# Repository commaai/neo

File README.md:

neo
=====

<b>NOTE: The NEO is deprecated. Check out the [latest hardware](https://github.com/commaai/hardware).

The neo is an open source robotics research platform. It is powered by a OnePlus 3 smartphone and an [STM32F205](http://www.st.com/en/microcontrollers/stm32f2x5.html?querycriteria=productId=LN1433)-based CAN interface board, in a 3d-printed housing with active cooling.

The neo platform includes [NEOS](https://github.com/commaai/eon-neos), a stripped down Android ROM designed for robustness and to get out of the way of your software. It also provides a modern linux environment for easy development.

Why
------

You cannot get a higher performance embedded processor than what's shipping in modern smartphones. They also come with an impressive array of sensors and radios, and are very low cost.

For some background see the work of [Android Based Robots](http://www.socsci.uci.edu/~jkrichma/ABR/abr_background.html).

Build
------

The neo is designed to be very easy to construct. You need to be able to shop online and use a soldering iron.

There is a **[very detailed guide](https://github.com/commaai/neo/raw/master/guide.pdf)** with instructions on what to order and how to build a neo.

to build a neo, 6 orders must be placed from the following sources:
- digikey
- mcmaster
- shapeways
- oshpark
- amazon
- oneplus

The total cost is about $700.

Directory structure
------

- board -- EagleCAD schematic, board, and library files
- parts -- csv bill of materials
- case -- stl files for 3d printing

Licensing
------

neo research platform is released under the MIT license.

**THIS IS ALPHA QUALITY SOFTWARE FOR RESEARCH PURPOSES ONLY. THIS IS NOT A PRODUCT.
YOU ARE RESPONSIBLE FOR COMPLYING WITH LOCAL LAWS AND REGULATIONS.
NO WARRANTY EXPRESSED OR IMPLIED.**

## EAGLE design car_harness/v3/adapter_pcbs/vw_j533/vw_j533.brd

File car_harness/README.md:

car harness
===

This is the documentation for the 26 pin connector on the car harness.

The car harness currently supports Honda Nidec, Honda Bosch, and Toyota. We would like to support more cars in the future.

Pull requests for additional pin outs are welcome. Please reference the open_pinout.sch.pdf file for adding new cars. This will guarantee the harness will work properly.

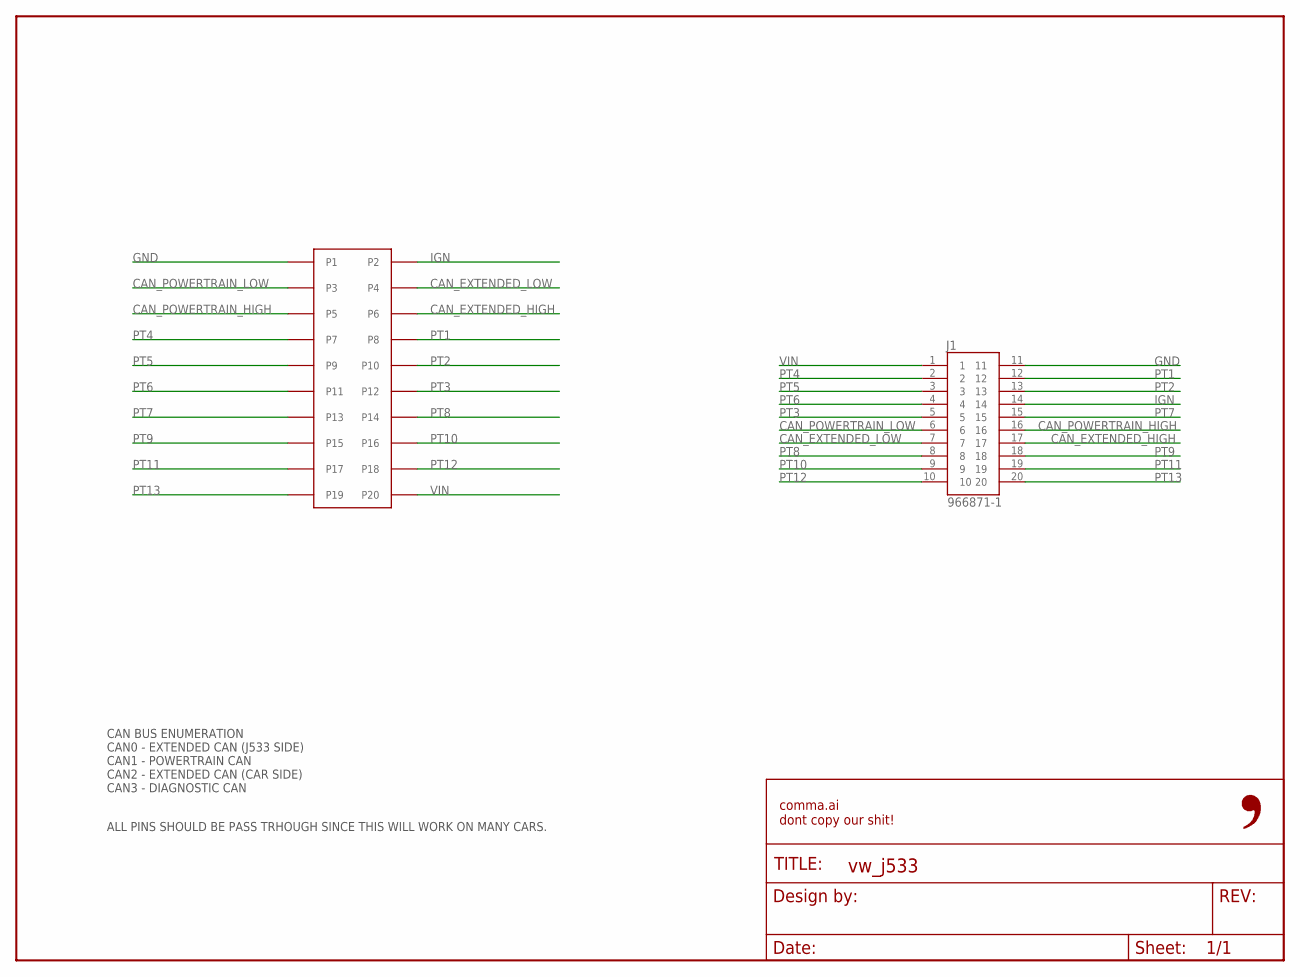
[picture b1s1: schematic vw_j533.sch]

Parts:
FRAME1: FRAME-LETTERNO_PACKAGE; DUMMY
J1: 966871-1; TE_966871-1
J2: 5018762040

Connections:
CAN_EXTENDED_HIGH: J1.17, J2.P6
CAN_EXTENDED_LOW: J1.7, J2.P4
CAN_POWERTRAIN_HIGH: J1.16, J2.P5
CAN_POWERTRAIN_LOW: J1.6, J2.P3
GND: J1.11, J2.P1
IGN: J1.14, J2.P2
PT1: J1.12, J2.P8
PT2: J1.13, J2.P10
PT3: J1.5, J2.P12
PT4: J1.2, J2.P7
PT5: J1.3, J2.P9
PT6: J1.4, J2.P11
PT7: J1.15, J2.P13
PT8: J1.8, J2.P14
PT9: J1.18, J2.P15
PT10: J1.9, J2.P16
PT11: J1.19, J2.P17
PT12: J1.10, J2.P18
PT13: J1.20, J2.P19
VIN: J1.1, J2.P20

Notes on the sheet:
CAN BUS ENUMERATION CAN0 - EXTENDED CAN (J533 SIDE) CAN1 - POWERTRAIN CAN CAN2 - EXTENDED CAN (CAR SIDE) CAN3 - DIAGNOSTIC CAN
ALL PINS SHOULD BE PASS TRHOUGH SINCE THIS WILL WORK ON MANY CARS.

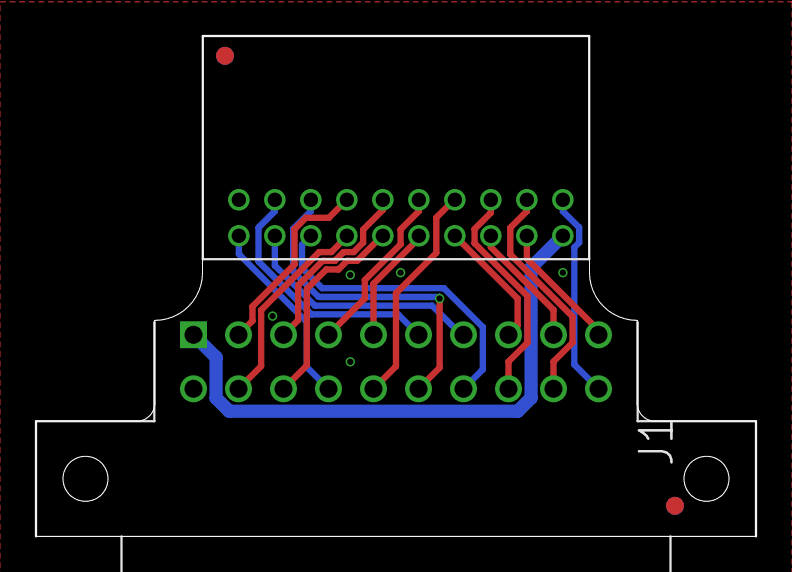
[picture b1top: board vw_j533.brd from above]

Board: 2 copper layers, 40.0 x 27.8 mm, 6 parts (1 on the bottom side), 20 nets.

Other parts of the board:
U$1: LOGO
U$2, U$3: FIDUCIAL

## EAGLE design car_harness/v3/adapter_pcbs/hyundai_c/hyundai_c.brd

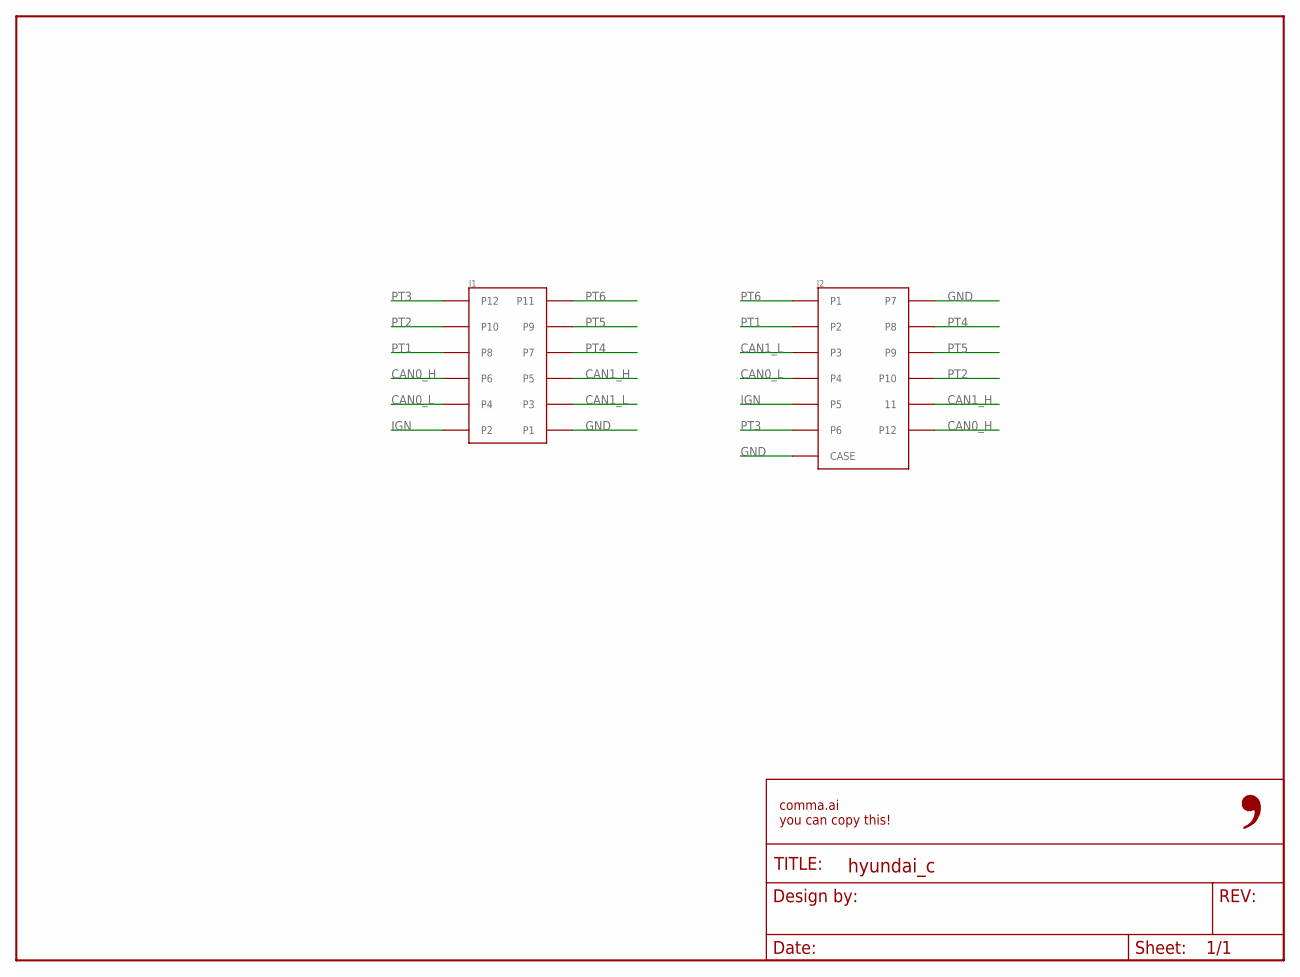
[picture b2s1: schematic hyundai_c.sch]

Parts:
FRAME1: FRAME-LETTER-OPENNO_PACKAGE; DUMMY
J1: 5018761240
J2: MG645845

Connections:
CAN0_H: J1.P6, J2.P12
CAN0_L: J1.P4, J2.P4
CAN1_H: J1.P5, J2.P11 (11)
CAN1_L: J1.P3, J2.P3
GND: J1.P1, J2.P7, J2.P$1 (CASE), J2.P$2 (CASE)
IGN: J1.P2, J2.P5
PT1: J1.P8, J2.P2
PT2: J1.P10, J2.P10
PT3: J1.P12, J2.P6
PT4: J1.P7, J2.P8
PT5: J1.P9, J2.P9
PT6: J1.P11, J2.P1

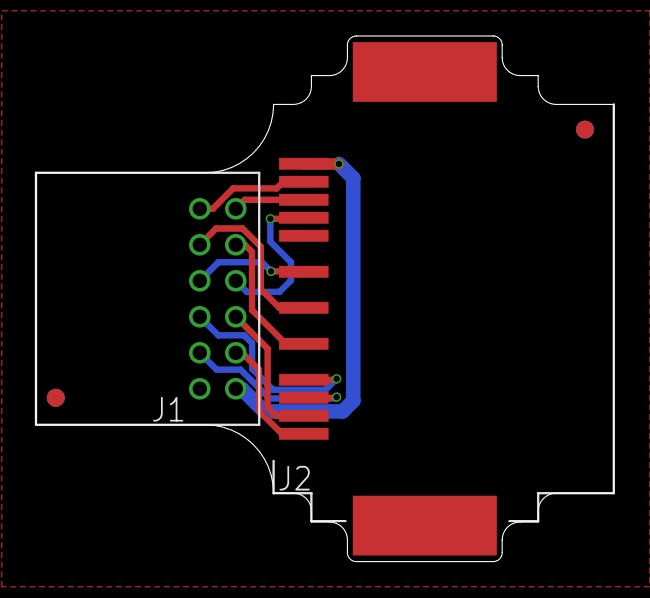
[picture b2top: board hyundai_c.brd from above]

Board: 2 copper layers, 32.1 x 29.2 mm, 6 parts (1 on the bottom side), 12 nets.

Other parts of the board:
U$1: LOGO
U$2, U$3: FIDUCIAL

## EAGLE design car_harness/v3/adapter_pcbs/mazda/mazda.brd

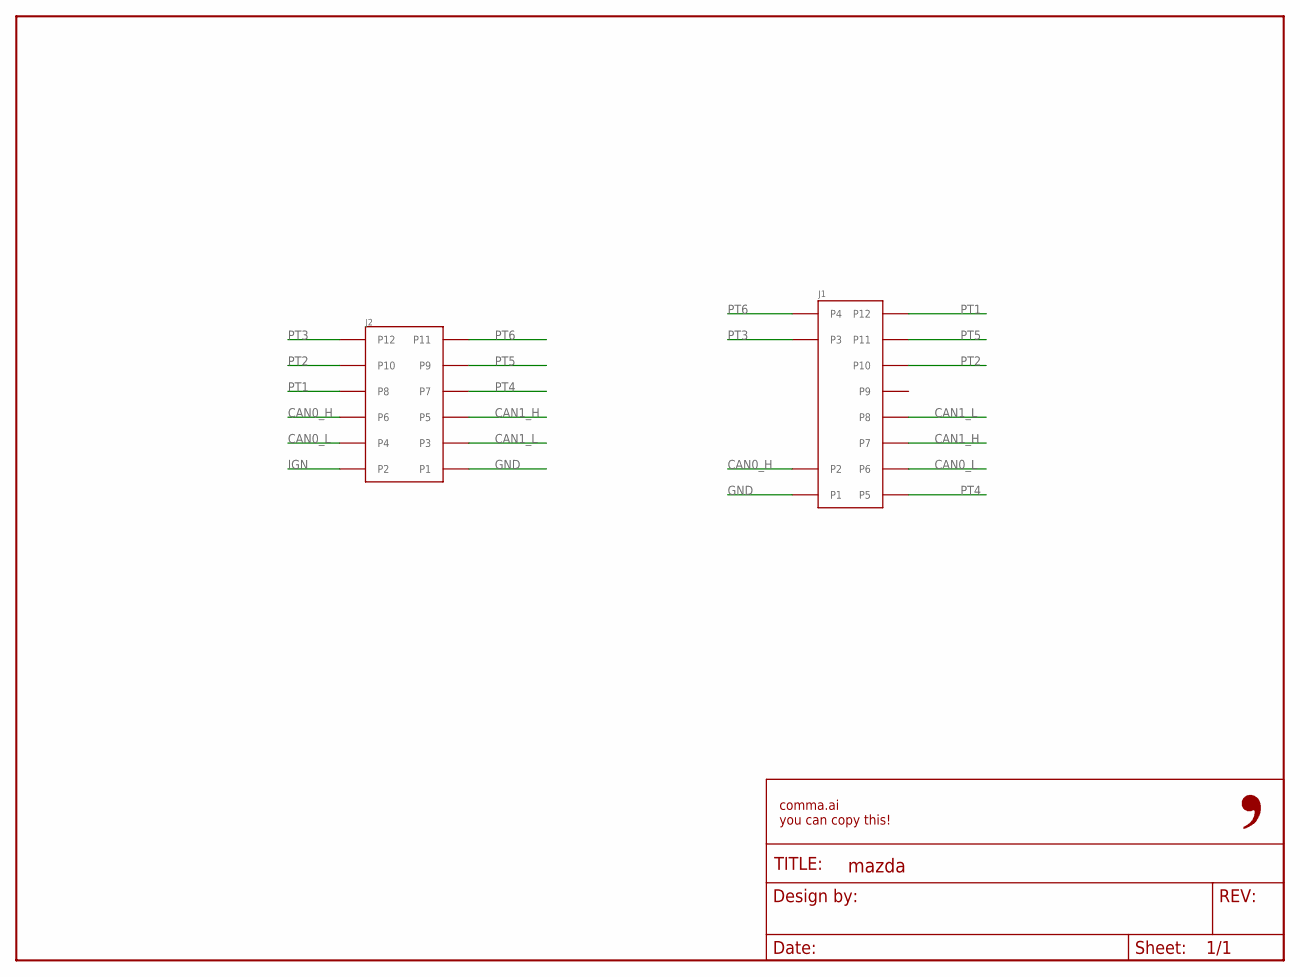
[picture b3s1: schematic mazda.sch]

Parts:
FRAME1: FRAME-LETTER-OPENNO_PACKAGE; DUMMY
J1: 0348260124
J2: 5018761240

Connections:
CAN0_H: J1.P2, J2.P6
CAN0_L: J1.P6, J2.P4
CAN1_H: J1.P7, J2.P5
CAN1_L: J1.P8, J2.P3
GND: J1.P1, J2.P1
IGN: J2.P2
PT1: J1.P12, J2.P8
PT2: J1.P10, J2.P10
PT3: J1.P3, J2.P12
PT4: J1.P5, J2.P7
PT5: J1.P11, J2.P9
PT6: J1.P4, J2.P11

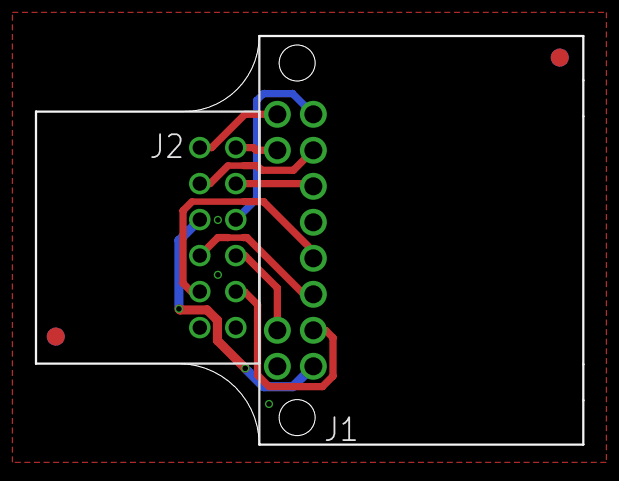
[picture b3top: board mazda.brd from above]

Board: 2 copper layers, 30.4 x 22.7 mm, 6 parts (1 on the bottom side), 11 nets.

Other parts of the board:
U$1: LOGO
U$2, U$3: FIDUCIAL

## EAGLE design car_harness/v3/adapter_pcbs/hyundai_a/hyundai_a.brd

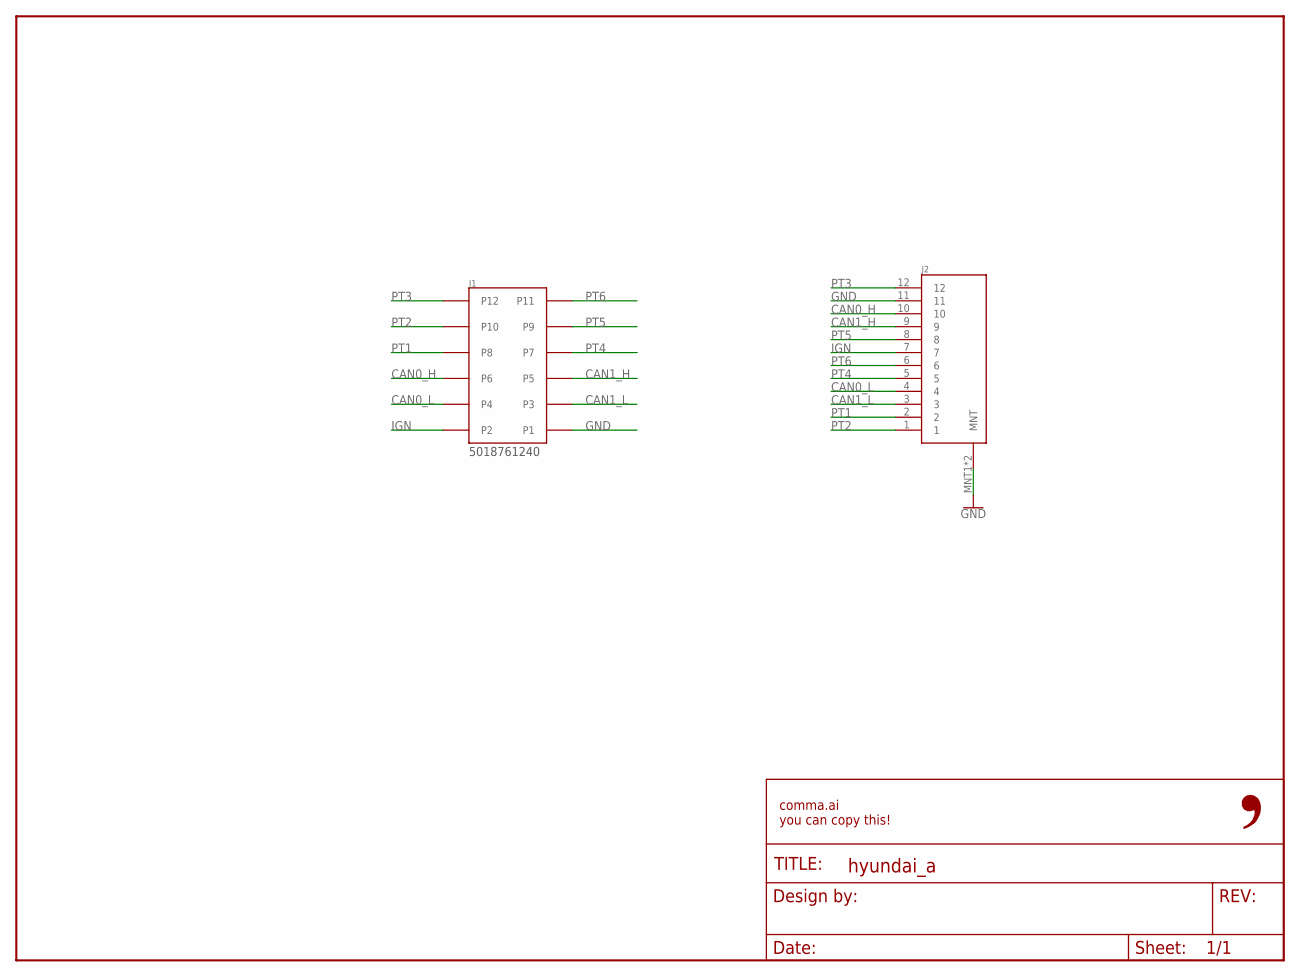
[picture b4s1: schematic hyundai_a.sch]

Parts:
FRAME1: FRAME-LETTER-OPENNO_PACKAGE; DUMMY
J1: 5018761240
J2: MG646151

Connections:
CAN0_H: J1.P6, J2.10
CAN0_L: J1.P4, J2.4
CAN1_H: J1.P5, J2.9
CAN1_L: J1.P3, J2.3
GND: J1.P1, J2.11, J2.MNT1 (MNT), J2.MNT2 (MNT)
IGN: J1.P2, J2.7
PT1: J1.P8, J2.2
PT2: J1.P10, J2.1
PT3: J1.P12, J2.12
PT4: J1.P7, J2.5
PT5: J1.P9, J2.8
PT6: J1.P11, J2.6

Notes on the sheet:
5018761240

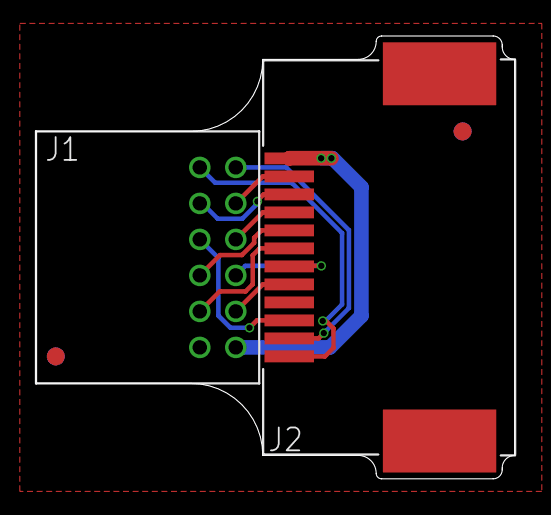
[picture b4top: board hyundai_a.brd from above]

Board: 2 copper layers, 26.6 x 24.6 mm, 6 parts (1 on the bottom side), 12 nets.

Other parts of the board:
U$1: LOGO
U$2, U$3: FIDUCIAL

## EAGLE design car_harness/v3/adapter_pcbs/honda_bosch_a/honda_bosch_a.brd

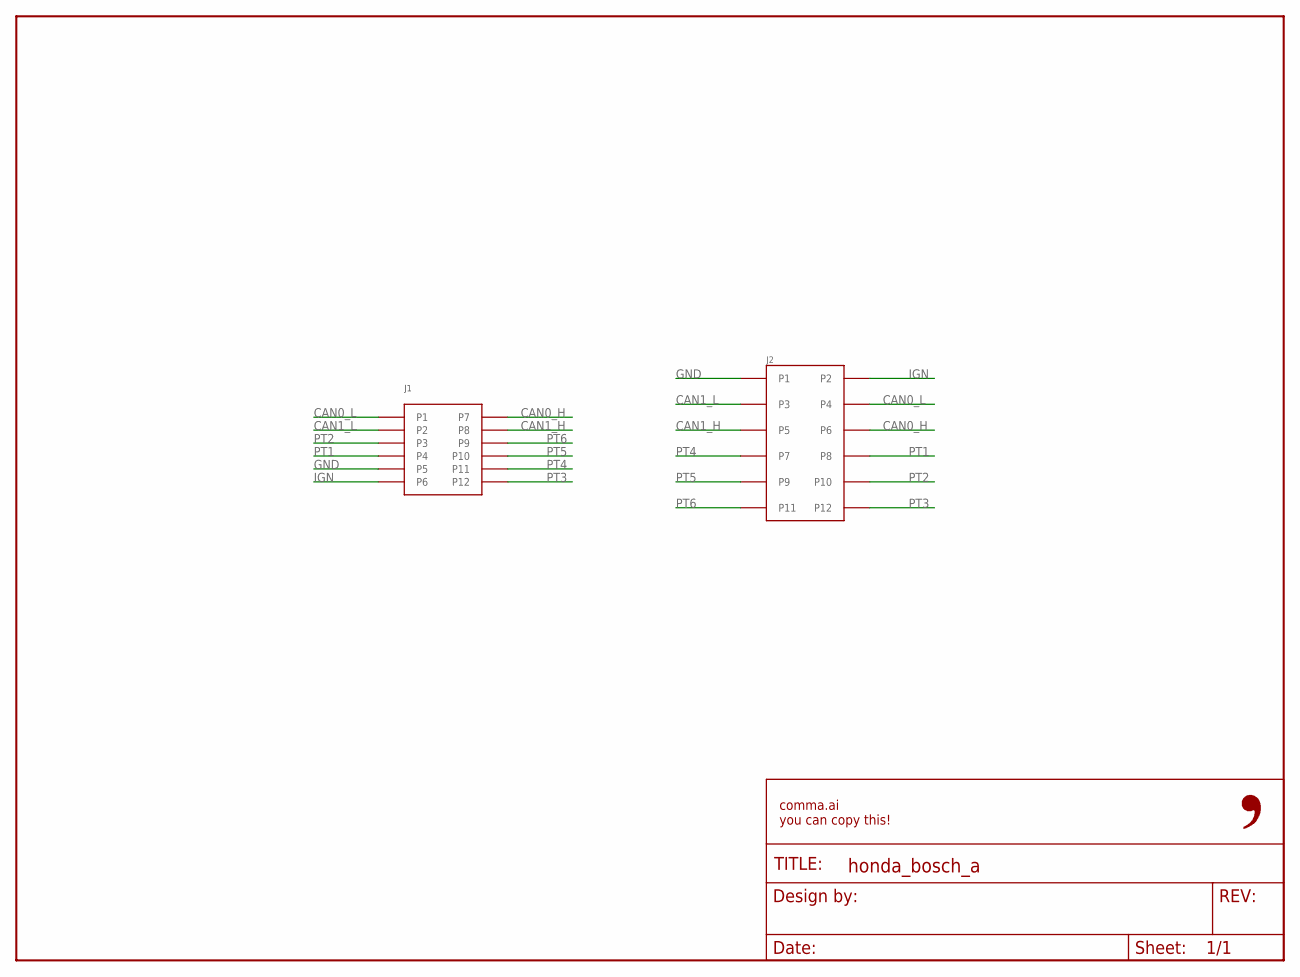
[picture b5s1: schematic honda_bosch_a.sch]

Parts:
FRAME1: FRAME-LETTER-OPENNO_PACKAGE; DUMMY
J1: MX34M12NF1
J2: 5018761240

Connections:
CAN0_H: J1.P7, J2.P6
CAN0_L: J1.P1, J2.P4
CAN1_H: J1.P8, J2.P5
CAN1_L: J1.P2, J2.P3
GND: J1.P5, J2.P1
IGN: J1.P6, J2.P2
PT1: J1.P4, J2.P8
PT2: J1.P3, J2.P10
PT3: J1.P12, J2.P12
PT4: J1.P11, J2.P7
PT5: J1.P10, J2.P9
PT6: J1.P9, J2.P11

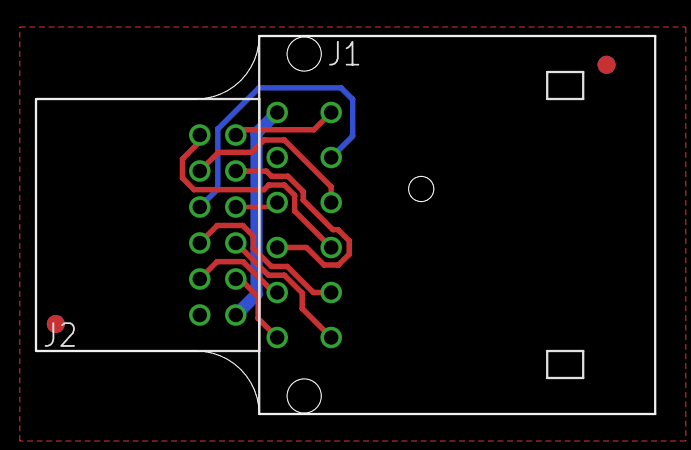
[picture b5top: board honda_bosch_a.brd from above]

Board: 2 copper layers, 34.4 x 21.0 mm, 6 parts (1 on the bottom side), 12 nets.

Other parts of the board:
E$1: LOGO
U$2, U$3: FIDUCIAL

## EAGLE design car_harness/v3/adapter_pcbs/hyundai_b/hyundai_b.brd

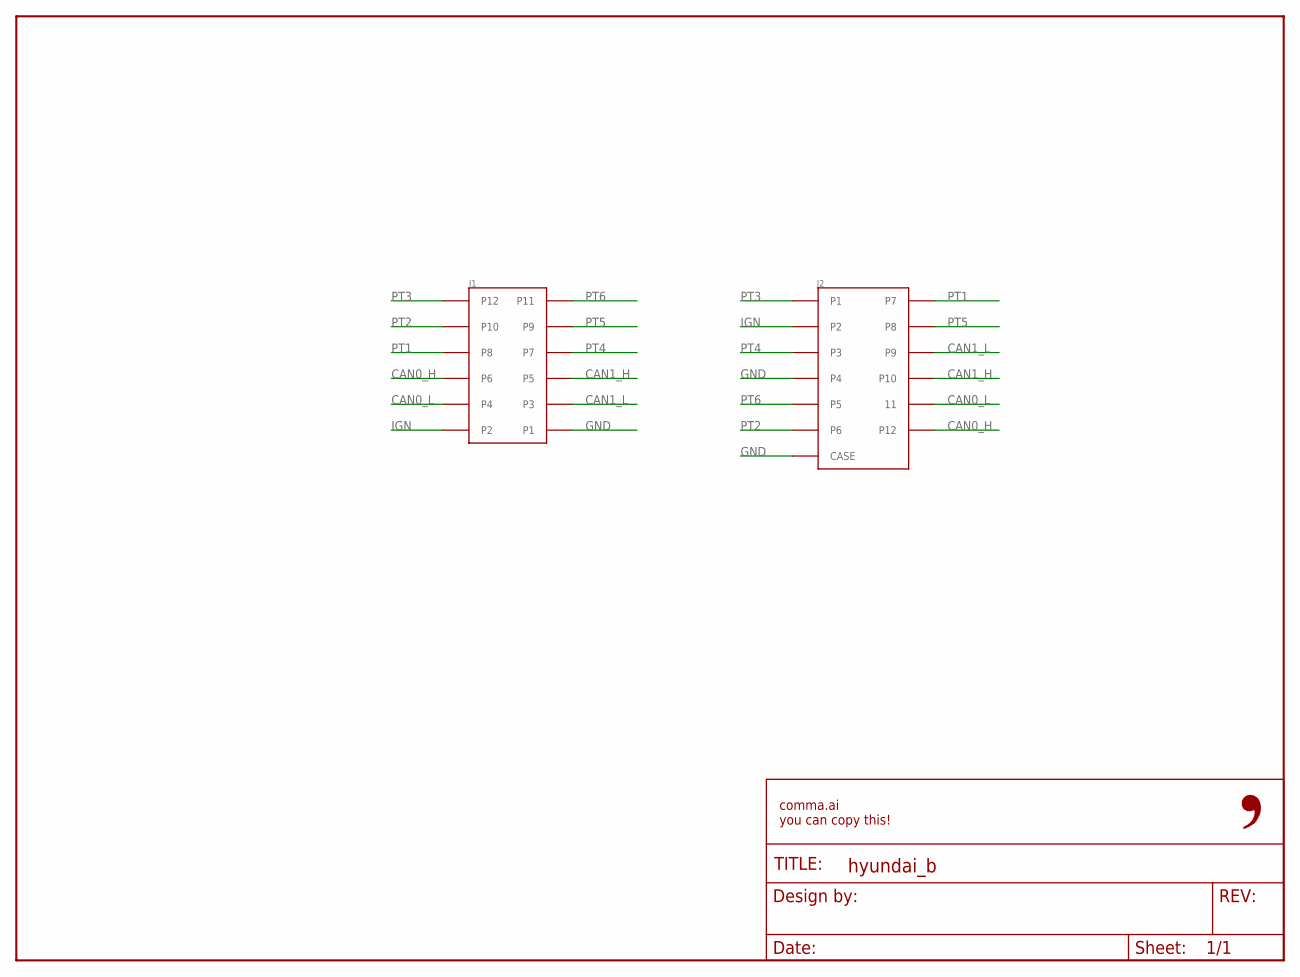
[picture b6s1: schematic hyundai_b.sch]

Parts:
FRAME1: FRAME-LETTER-OPENNO_PACKAGE; DUMMY
J1: 5018761240
J2: MG645845

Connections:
CAN0_H: J1.P6, J2.P12
CAN0_L: J1.P4, J2.P11 (11)
CAN1_H: J1.P5, J2.P10
CAN1_L: J1.P3, J2.P9
GND: J1.P1, J2.P4, J2.P$1 (CASE), J2.P$2 (CASE)
IGN: J1.P2, J2.P2
PT1: J1.P8, J2.P7
PT2: J1.P10, J2.P6
PT3: J1.P12, J2.P1
PT4: J1.P7, J2.P3
PT5: J1.P9, J2.P8
PT6: J1.P11, J2.P5

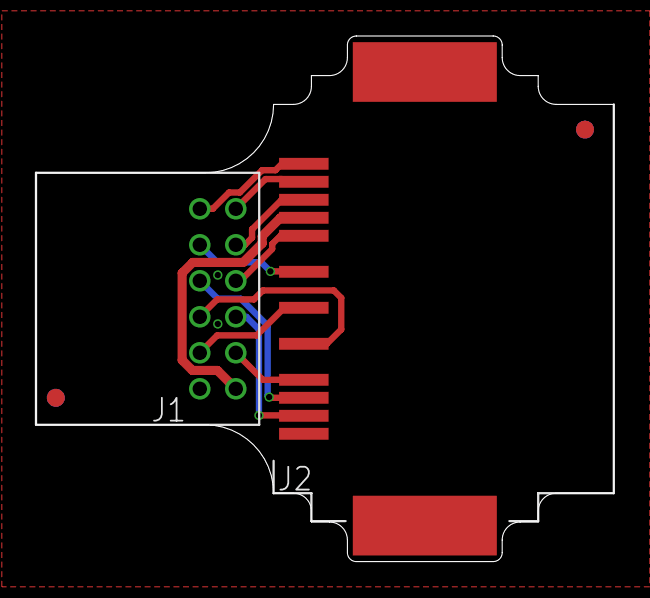
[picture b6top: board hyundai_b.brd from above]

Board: 2 copper layers, 32.1 x 29.2 mm, 6 parts (1 on the bottom side), 12 nets.

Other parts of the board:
U$1: LOGO
U$2, U$3: FIDUCIAL

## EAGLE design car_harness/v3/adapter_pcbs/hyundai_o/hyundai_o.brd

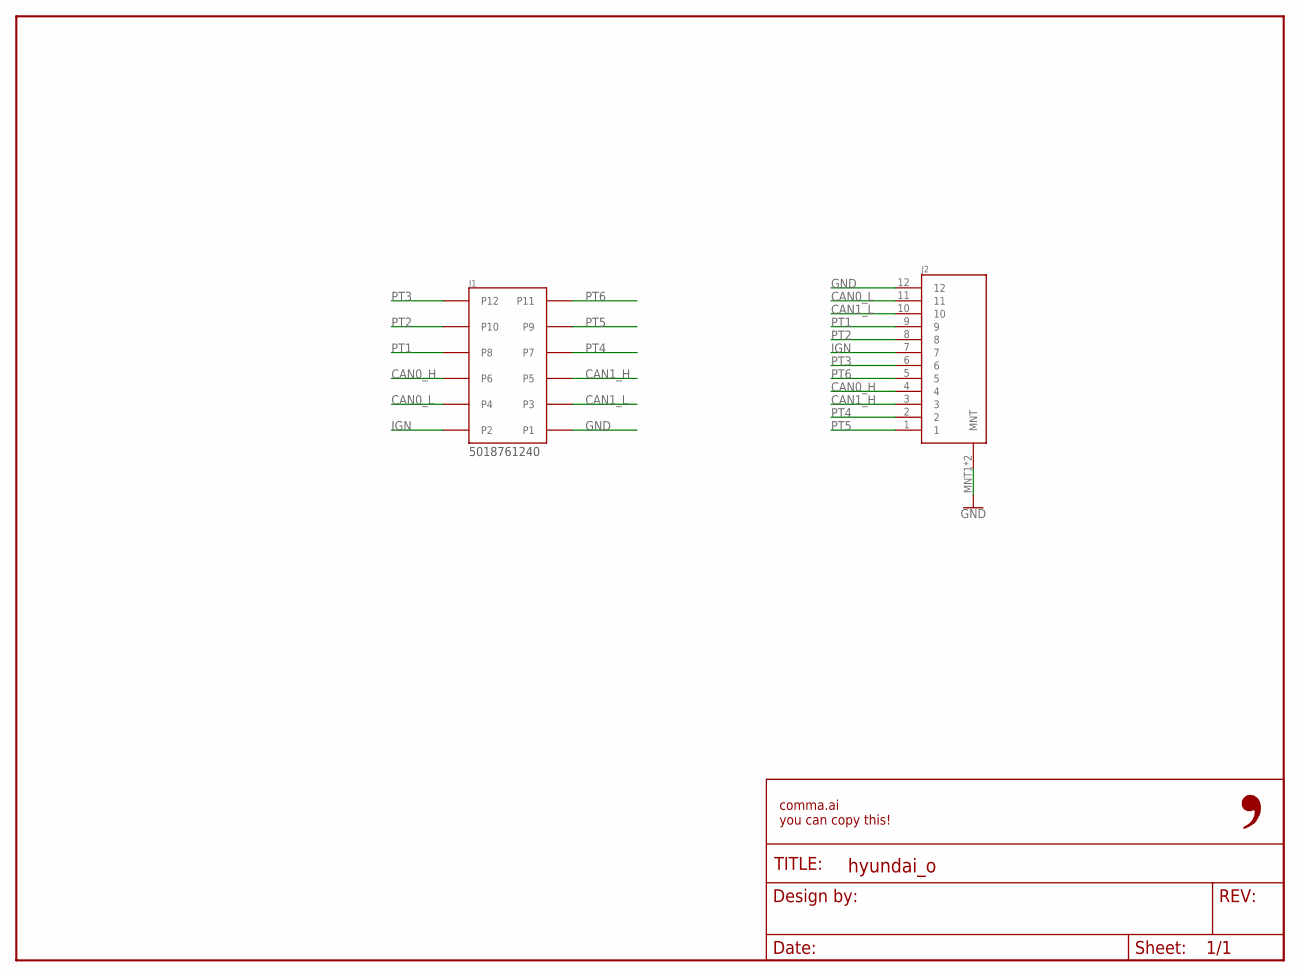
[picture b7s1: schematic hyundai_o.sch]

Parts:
FRAME1: FRAME-LETTER-OPENNO_PACKAGE; DUMMY
J1: 5018761240
J2: MG646151

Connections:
CAN0_H: J1.P6, J2.4
CAN0_L: J1.P4, J2.11
CAN1_H: J1.P5, J2.3
CAN1_L: J1.P3, J2.10
GND: J1.P1, J2.12, J2.MNT1 (MNT), J2.MNT2 (MNT)
IGN: J1.P2, J2.7
PT1: J1.P8, J2.9
PT2: J1.P10, J2.8
PT3: J1.P12, J2.6
PT4: J1.P7, J2.2
PT5: J1.P9, J2.1
PT6: J1.P11, J2.5

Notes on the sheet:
5018761240

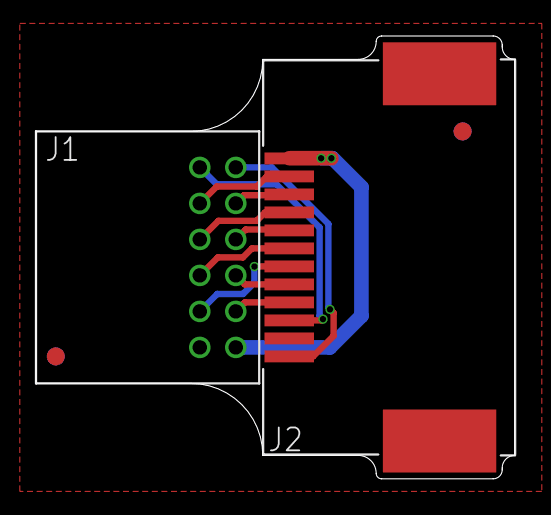
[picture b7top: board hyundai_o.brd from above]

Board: 2 copper layers, 26.6 x 24.6 mm, 6 parts (1 on the bottom side), 12 nets.

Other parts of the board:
U$1: LOGO
U$2, U$3: FIDUCIAL

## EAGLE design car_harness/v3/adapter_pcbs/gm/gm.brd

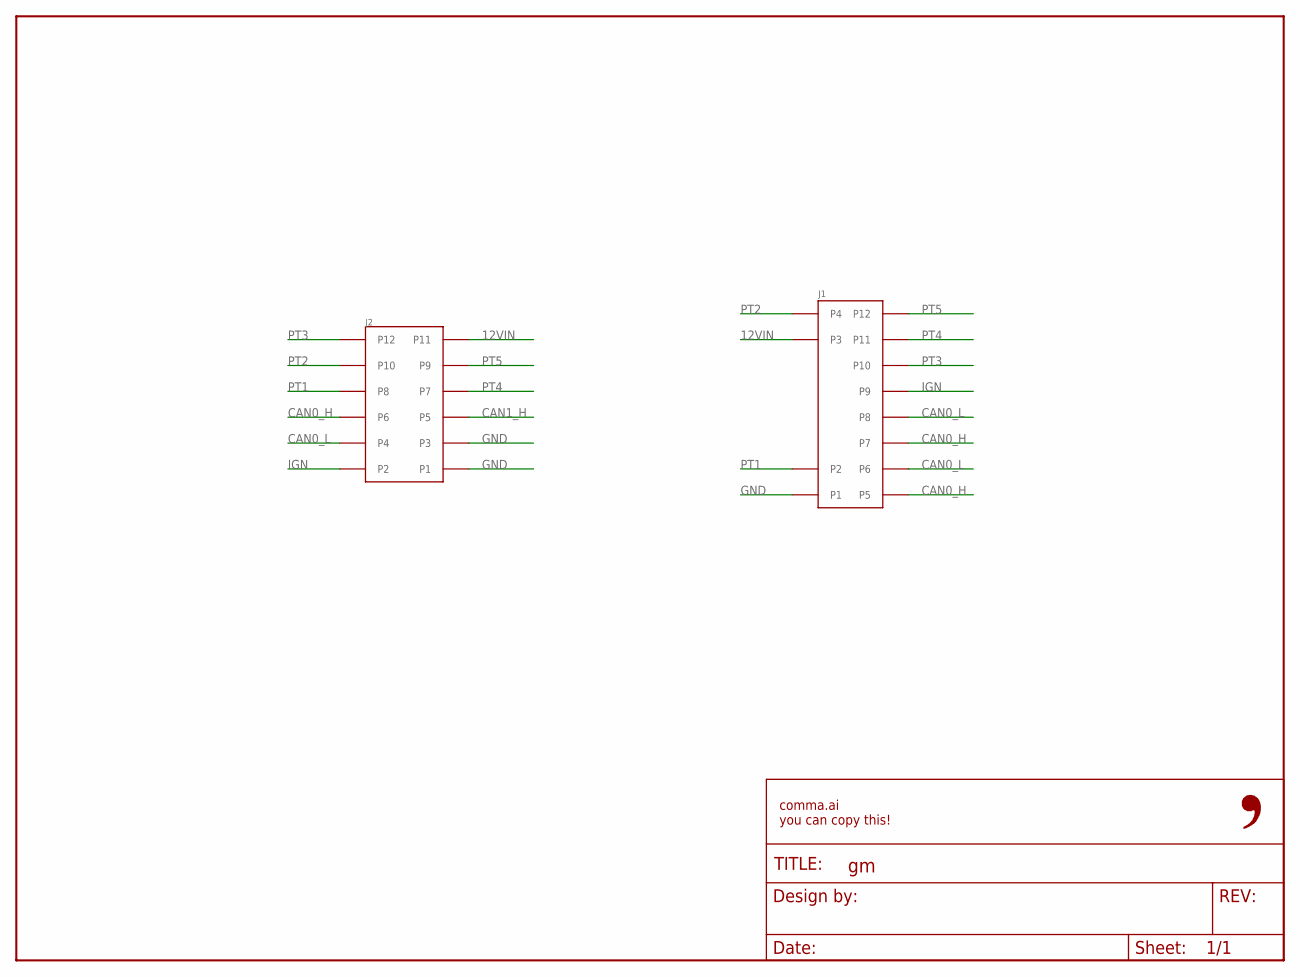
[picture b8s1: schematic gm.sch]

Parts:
FRAME1: FRAME-LETTER-OPENNO_PACKAGE; DUMMY
J1: 0348260124
J2: 5018761240

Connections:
12VIN: J1.P3, J2.P11
CAN0_H: J1.P5, J1.P7, J2.P6
CAN0_L: J1.P6, J1.P8, J2.P4
CAN1_H: J2.P5
GND: J1.P1, J2.P1, J2.P3
IGN: J1.P9, J2.P2
PT1: J1.P2, J2.P8
PT2: J1.P4, J2.P10
PT3: J1.P10, J2.P12
PT4: J1.P11, J2.P7
PT5: J1.P12, J2.P9

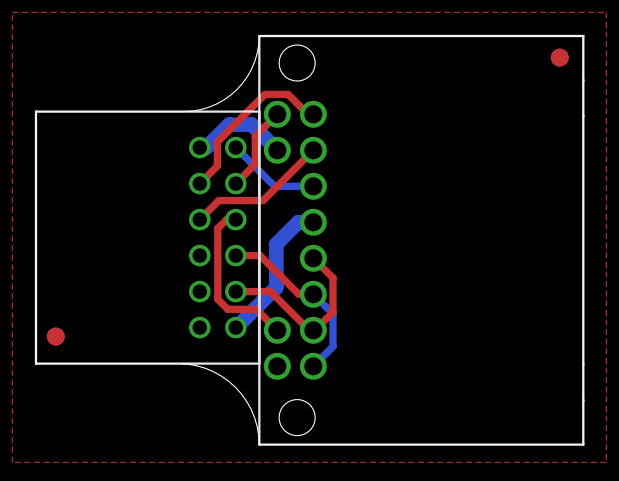
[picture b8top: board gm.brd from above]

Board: 2 copper layers, 30.4 x 22.7 mm, 6 parts (1 on the bottom side), 10 nets.

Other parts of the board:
U$1: LOGO
U$2, U$3: FIDUCIAL

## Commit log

2016-11-30 files and guide
2016-11-30 adding license to guide
2016-11-30 broken link
2016-12-01 fixing broken links in guide, sorry yall
2016-12-01 Make compatible with kitnic.it
2016-12-01 Add note about kitnic.it page to README
2016-12-10 fixing typos
2016-12-13 adding schematic pdf for github viewing
2016-12-29 macrofab placement bom & placement
2017-01-05 fixing part orientation on macrofab file
2017-01-27 gopro adhesive compatible mount
2017-02-22 updated digikey&macrofab BOM after USB out of stock, schematic cleanup
2017-06-02 push GIANTpanda w/ dual rj45 pinouts, many updates to comma.ai eagle library
2017-06-04 add LED polarity placement to PCB, push digikey BOM
2017-06-28 silkscreen polarity indicator for optional LED was on the wrong side
2017-09-23 many library updates
2017-09-23 honda giraffe
2017-09-25 honda mirror to gopro slide adapter
2017-10-09 remove unsupported giant panda
2017-10-10 push honda giraffe case
2017-10-12 honda giraffe readme
2017-10-19 toyota giraffe push, update honda BOM with new screws
2017-11-20 missing Honda LKAS indicator, Honda LKAS2EPS now passed thru, pass thru all unused Toyota pins
2017-11-20 add readme and card
2017-11-20 image fixes for readme
2017-11-20 toyota case stl
2017-11-25 fixed digikey product links
    the digikey links with dksus.dll in them do not work
2017-11-25 fixed honda giraffe digikey product links
    the digikey links with dksus.dll in them do not work
2017-12-19 update mirror to gopro adapter for production eon
2018-01-26 toyota BOM was missing DC barrel connector
2018-02-07 eon mounts 22-30deg .stls
2018-02-22 giraffe schematics as pdf
2018-03-01 antenna mount stl is open!
2018-03-01 rotate for printing
2018-03-06 fix digikey links
2018-03-14 flipped cam connector for odyssey
2018-03-14 made a drill for power bigger
2018-03-29 comma pedal push
2018-03-29 add readme and license
2018-03-29 more accurate readme
2018-03-29 add picture of pedal
2018-03-29 improve readme
2018-03-29 small
2018-03-29 fw link
2018-03-29 updated pedal BOM for out of stock cap
2018-04-01 deprecated
2018-04-03 pushing simple build guide
2018-04-06 Bosch Honda Giraffe
2018-04-24 push panda debug board
2018-05-13 J1 and J2 MobilEye Connector Numbers
    Moved the numbers so that they are in the correct order. Makes for better debugging and less mistakes
2018-06-06 move into nidec
2018-06-07 Bosch Giraffe v2
    - Remove fan crap
    - Add in fake ethernet (Can 3 vs can 2, because of existing giraffes in
    the field)
    - Drops panda down for USB clearance issues with headliner on Civic
    Hatch
    - Stock camera is always powered. Disable via CAN disconnects with
2018-06-07 fix the connector name and row height
    row height was about 3.86mm. should be 3.6mm, else stress on the
    factory harness connector occurs.
2018-06-07 Odyssey/TLX board
2018-06-07 Readme, BOM and Case
2018-06-07 Changed folder name to nidec_inverted
2018-06-19 Shade
2018-06-19 Universal ball joint mount
2018-06-22 Added design files
2018-06-22 Added gerbers and BOM
2018-06-22 Added OSHPark shared design
2018-07-13 Change OBDII_female
    Change original OBDII_female and replace it with pads layout to allow for 90 degree OBDII_female installation.
2018-08-07 Push Bosch Giraffe
2018-08-07 fix .png
2018-08-07 Fixed typo
2018-08-07 Make sch.pdf more readable
2018-08-11 Revert "Create README.md"
2018-08-19 Update Bosch Case and BOM
2018-08-20 grey panda antenna mount 28 degrees by @mhevery
2018-09-09 giraffe for Chrysler Jeep and Dodge
2018-09-09 add images of board and schematic
2018-09-10 increase the width of some routes
2018-09-10 move the mini50 posts to the correct locations
2018-09-11 fix comma.ai.lbr so I'm not overwriting an existing device
2018-09-11 updated board image with new post hole locations for mini50
2018-09-11 Calbi Opensource day
2018-09-13 Update sch and push case
2018-09-18 Update Hyundai Giraffe Case to give room to depress camera clip
2018-10-24 Added a small capacitor on the GMLan pin for stability
2018-10-24 Updated BOM (added cap and some available parts suggestions)
2018-10-24 Added OBD++ file for macrofab
2018-10-24 Updated gerbers (added capacitor)
2018-10-31 Added updated OSHPark shared design
2018-11-07 simple giraffe design for CJD
2018-11-13 Fix BOM, flip J1 and J2 so parts match
2018-11-22 Push Inverted Nidec Giraffe
2018-12-18 Flowchart in PNG, replace text in README.md
    Also added note that comma power should connect to car's OBD port.
2018-12-19 add 3d printed case for giraffe-cjd-simple by @mhevery
2019-01-05 Point to new NEOS repo
2019-01-14 chrysler pacifica fuses to reboot the car
2019-02-02 🦒 Giraffe for Chrysler, Jeep, and Dodge (#42)
    * giraffe for Chrysler Jeep and Dodge
2019-02-05 Push FCA Giraffe
2019-02-05 fix links in FCA BOM
    What gauge header pins do you put in your crimps?
2019-02-05 fix links in FCA BOM (#44)
    What gauge header pins do you put in your crimps?
2019-02-05 add header pins for fca
2019-02-06 update resistor part with correct one
2019-02-15 Opensource GM Interface Board thanks to vtarasov
2019-04-01 Toyota Flowchart resistor update
    Update Toyota Giraffe Switch Settings Flowchart to note cars that require resistor.
2019-04-02 Move switch card images to individual giraffe folders
    Remove the switch card image from the main giraffe readme and add it to readme for each type of giraffe.
2019-04-02 Move switch card images to individual giraffe folders (#49)
    Remove the switch card image from the main giraffe readme and add it to readme for each type of giraffe.
2019-04-02 Toyota Flowchart resistor update (#48)
    Update Toyota Giraffe Switch Settings Flowchart to note cars that require resistor.
2019-04-02 Revert "Toyota Flowchart resistor update (#48)"
    This reverts commit e825879428b67c9a77ed8ea770e7d3340e7e84cc.
2019-04-02 Revert "Toyota Flowchart resistor update (#48)" (#50)
    This reverts commit e825879428b67c9a77ed8ea770e7d3340e7e84cc.
2019-04-08 Fix GM Giraffe typos
    - Missing C18 in digikey.csv.
    - For DFU, BOOT needs to be pulled high, not low.
2019-04-08 Fix GM Giraffe typos (#51)
    - Missing C18 in digikey.csv.
    - For DFU, BOOT needs to be pulled high, not low.
2019-04-23 Subaru Giraffe push
2019-05-14 Toyota Giraffe: Add resistor
2019-05-19 giraffe schematics as pdf: Add resistor"
2019-05-19 giraffe schematics as pdf: Add resistor" (#52)
2019-07-07 Fix link in README.md
2019-07-08 Fix link in README.md (#53)
2019-08-09 grey panda: flat antenna mount
2019-08-12 FCA Giraffe: Add PDF
2019-10-10 car harness: opensource pin outs and block diagrams
2019-10-19 Car Harness: Add Subaru harness diagram
2019-11-08 Car Harness: Fix Subaru CAN lines
2019-11-13 open_pinout: Add new RJ45 pin out
2019-12-04 Car Harness: Update for additional PT wires for Lexus
2020-01-12 open OBD-C standard
2020-01-12 FCA Harness PDF
2020-01-21 Updated OBDII-C Pinout
    A more user friendly visual of OBDII-C connector configuration.
2020-01-22 Updated OBDII-C Pinout (Removed Male USB-C)
2020-01-23 Updated OBDII-C Pinout
    Added SBU line comments.
2020-01-23 comma2: STL for mount
2020-02-01 EON: New mount adapter for big mounts
2020-02-06 Corrected SBU1 to SBU2 in Notes.
2020-02-12 Add harness board schematic
2020-02-13 Update harness board schematic
2020-02-16 Fix OBD-C pinout notes
2020-03-31 Car Harness: Add Hyundai and VW PDF's
2020-04-06 Car Harness: Add Nissan
2020-04-24 comma2 : push new mount
2020-05-06 Car Harness: Sonata Wire Harness
2020-05-13 Update README: All about the comma two now
2020-06-05 Car Harness: Update VW connector P/Ns
2020-07-08 Car Harness: Update for new Bosch connector
2020-07-23 Genesis Harness
2020-07-29 Car Harness: Update Genesis
2020-09-15 Gerber ZIP
2020-10-02 Car Harness:CAN0 -> CAN2
2020-11-21 Comma Key: Push Key
2021-03-02 Car Harness: Nissan now has A and B types
2021-08-02 comma three
2021-08-23 Car Harness: Correct JAE P/N
2021-09-07 Car Harness: add J533 harness
2021-10-15 STL of printable comma 3 mount
2021-10-29 Tesla AP2+ harness schematics
2021-11-09 Push mazda harness and guide
2021-12-11 push harness adapter boards
2022-02-14 Hyundai: add new wiring type
2022-05-08 Body: add C3 stand STL
2022-06-17 Kia EV6 Harness and board
2022-07-08 Car Harness: Update Bosch harnesses
2022-09-17 GM Cam Harness Sxhematic Updates * Tie IGN to GND to avoid heat-related false starts * Make two extra wires (for camera pins 2 and 12) standard * Show 10-pin adapter board for car-side connector
2022-09-17 Add GM Camera Harness schematic
2022-09-17 GM Mini Adapter board
2022-09-27 Car harness: Push GM/Bolt harness
2022-09-27 Car harness: Ford Q3
2022-11-17 Car Harness: push 3D printed connectors
2022-12-12 Car Harness: Add new harnesses
2022-12-15 Car Harness: Add RAM
2023-02-09 Push 8 degree C3 mount
2023-06-12 Car Harness: Update Mazda diagram
2023-07-19 Car Harness: Updated Ford Q4
2023-07-31 3X: Mounts
2023-08-07 Car Harness: Toyota A and B
2023-08-29 Car Harness: Additional PT lines on Toyota B
2023-09-21 Car Harness: Subaru D
2023-09-29 Car Harness: Update CAN numbering
2023-12-09 add white panda guide
2023-12-14 body: add hat and wheeled stand
2024-02-22 Nidec Harness for Fit Hybrid JDM
    It is similar to Clarity. But control can be done using a single power train CAN line.
2024-07-05 opensource harness v3 schematics
2024-07-05 remove weird schematic
2024-07-26 update j533
2024-07-26 update Ford Q4 and RAM connector part numbers
2024-07-31 comma 3X
2024-08-01 fix J533 harnesses
2024-09-03 update J533 schematic
2025-02-17 new hw repo
